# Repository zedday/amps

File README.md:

AMPS
---

AMPS is an **A**TX **M**ade **P**ower **S**upply.  
It's based on a recovery pc power supply with a little elecronics and a 3d printed cover.

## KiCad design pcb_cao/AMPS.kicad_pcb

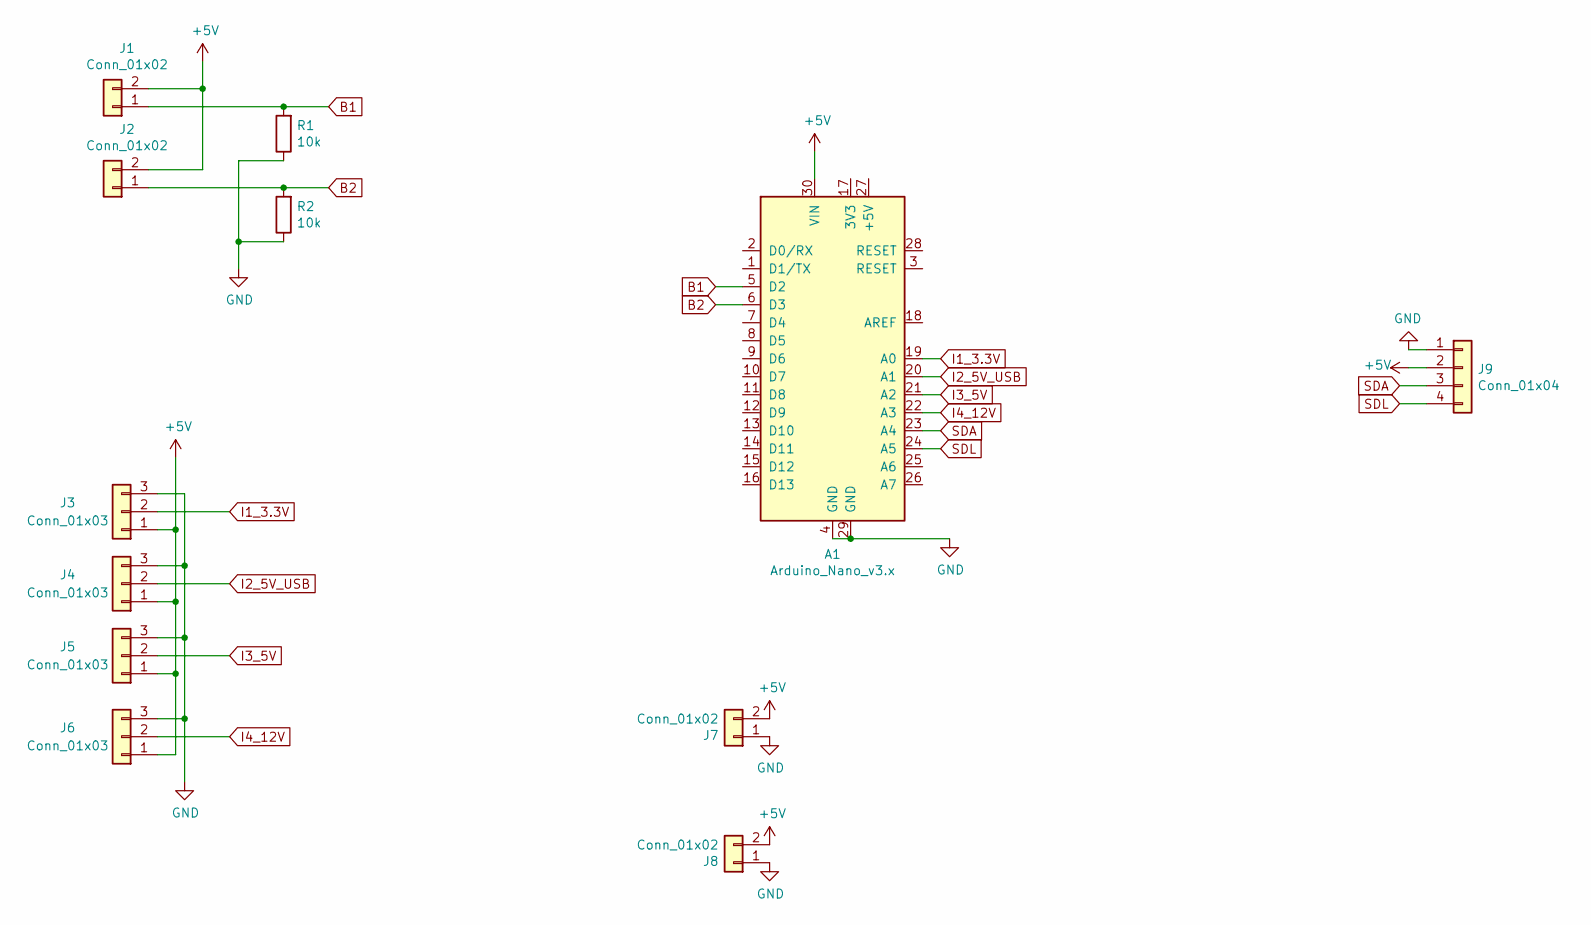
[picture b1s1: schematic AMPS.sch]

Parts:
A1: Arduino_Nano_v3.x; Arduino_Nano
J1, J2, J7, J8: Conn_01x02; PinHeader_1x02_P2.54mm_Vertical
J3, J4, J5, J6: Conn_01x03; PinHeader_1x03_P2.54mm_Vertical
J9: Conn_01x04; PinHeader_1x04_P2.54mm_Vertical
R1, R2: 10k; R_Axial_DIN0207_L6.3mm_D2.5mm_P10.16mm_Horizontal

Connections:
+5V: A1.30 (VIN), J1.2, J2.2, J3.1, J4.1, J5.1, J6.1, J7.2, J8.2, J9.2
B1: A1.5 (D2), J1.1, R1.2
B2: A1.6 (D3), J2.1, R2.2
GND: A1.4 (GND), A1.29 (GND), J3.3, J4.3, J5.3, J6.3, J7.1, J8.1, J9.1, R1.1, R2.1
I1_3.3V: A1.19 (A0), J3.2
I2_5V_USB: A1.20 (A1), J4.2
I3_5V: A1.21 (A2), J5.2
I4_12V: A1.22 (A3), J6.2
SDA: A1.23 (A4), J9.3
SDL: A1.24 (A5), J9.4

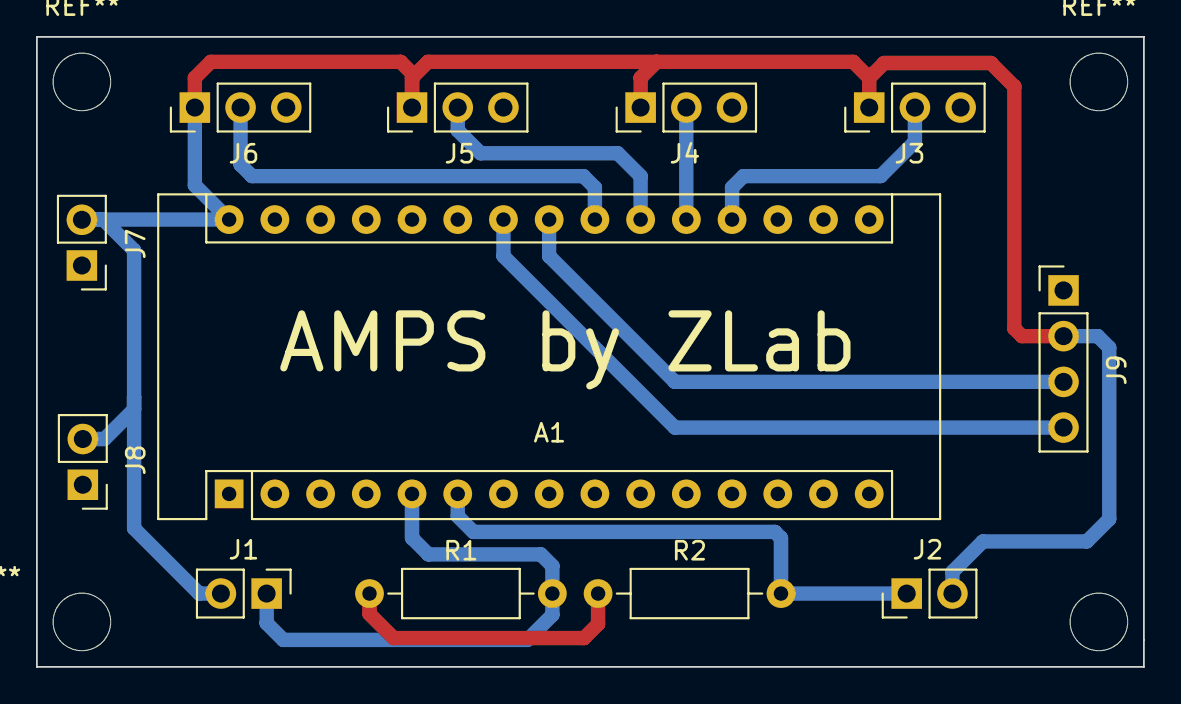
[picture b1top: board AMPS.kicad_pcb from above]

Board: 2 copper layers, 61.5 x 35.0 mm, 12 parts (0 on the bottom side), 10 nets.

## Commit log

2019-10-06 3D printable cover
2019-10-08 Move the screen location 1mm to the bottom
2019-10-14 Some adjustments
2019-10-28 Add documents folder to gitignore
2019-10-28 Source code initial commit
2019-10-28 Add screen header Add printLCD function
2019-11-01 Fix routing problems
    - Duplicate pins tag on the LCD connexion
    - Fix Footprints references
    - Increase vias diameter
2019-11-01 Power the arduino micro by pin 'Vin' not pin '5V'
2019-11-16 Using an I2C LCD Screen
2019-11-17 Redesign of the PCB
    Use a I2C LCD screen
    Use only 2 buttons
